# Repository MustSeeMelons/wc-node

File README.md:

# WC internet radio

Inspired by a restroom that welcomed me as I entered, played smooth jazz while I was inside, and even said goodbye as I left. A Raspberry Pi Zero W at the heart.

All audio playback is based on [this Adafruit article](https://learn.adafruit.com/adafruit-max98357-i2s-class-d-mono-amp/raspberry-pi-wiring).

Legacy 32-bit Pi OS is required for this to work.

## V1

Turns out using a sonar distance sensor for presence detection does not work very well. You might enter the room and stay out of range for a bit, thus triggering a leave. Then after a bit re-trigger it. Many edge cases, for proper operation switch should be on the door and the door must be auto-closing. Otherwise the user experience will be flawed.

Kept the sonar as the on/off switch. Made to just work without spending much time on the looks.

Consists of a Pi Zero W, MAX98357 and a HC-SR04. Everything is powored from the Pi. Suprisingly, sounds better than most laptops.

## V2

While the V1 worked well, it did not look the part. Also the sonar was a gimmick and it lacked physical volume controls that turned out more important than anticipated.

The sonar was replaced with a switch and a rotary encoder entered the fray. Turn it on/off with the switch and adjust the volume with the ring around the speaker.

Worked well enough, but it sounded worse. Propably because the speaker was not as enclosed as it was previsouly. The ring was also flimsy feeling. For some reason I used a rotary encoder from a mouse. Which is tiny and made positioning it harder. Also bearings would have been nice.

## V3

Time to make it louder and make it look even nicer. Made possible by a bunch of interconencted modules: 12V power to an Aliexpress amplifirer. Buck/boost module to step down 12V to 5V for the Pi. An PCM5102A module for turning the Pi's I2S signal into analogue audio. Non removable 12V power brick.

Operation requires pressing a button to turn on audio playback from the Pi and turning nob to turn off the amp and perform volume control.

Sounds better and overall is much more pleasing to the eye.

## V4

The final iteration: getting rid of the rats nest of modules and making an integrated PCB for all. About 1.5 years of learning electronics made it possible.

It works better as ever and propably is the final form.

Is it perfect? Hell no, but functional without major flaws as far as I know. The PCB layouts ignore `recomended layouts` from the datasheets so to be easier to hand solder.

The speaker size really should be placed into a wooded enclosure. Also the [stream](https://fmstream.org/) quality is a factor now.

# How to

- `sudo apt-get update`
- `npm i`
- `sudo apt-get install -y mpg123`
- `sudo npm start`
- `/etc/systemd/system/ateja.service`

# Node

- `use nvm to install node`
- `sudo ln -s $(which node) /usr/bin/node`
- `sudo ln -s $(which npm) /usr/local/bin/npm`

# A few commands to add to /boot/config.txt

`raspi-gpio set 20 pu`
`raspi-gpio set 4 pu`

# Systemd

- `sudo systemctl daemon-reload`
- `sudo systemctl start ateja`
- `journalctl -u ateja.service -f`
- `sudo systemctl status ateja`
- `sudo systemctl stop ateja`
- `sudo systemctl restart ateja`
- `sudo systemctl enable ateja`
- `sudo systemctl disable ateja`

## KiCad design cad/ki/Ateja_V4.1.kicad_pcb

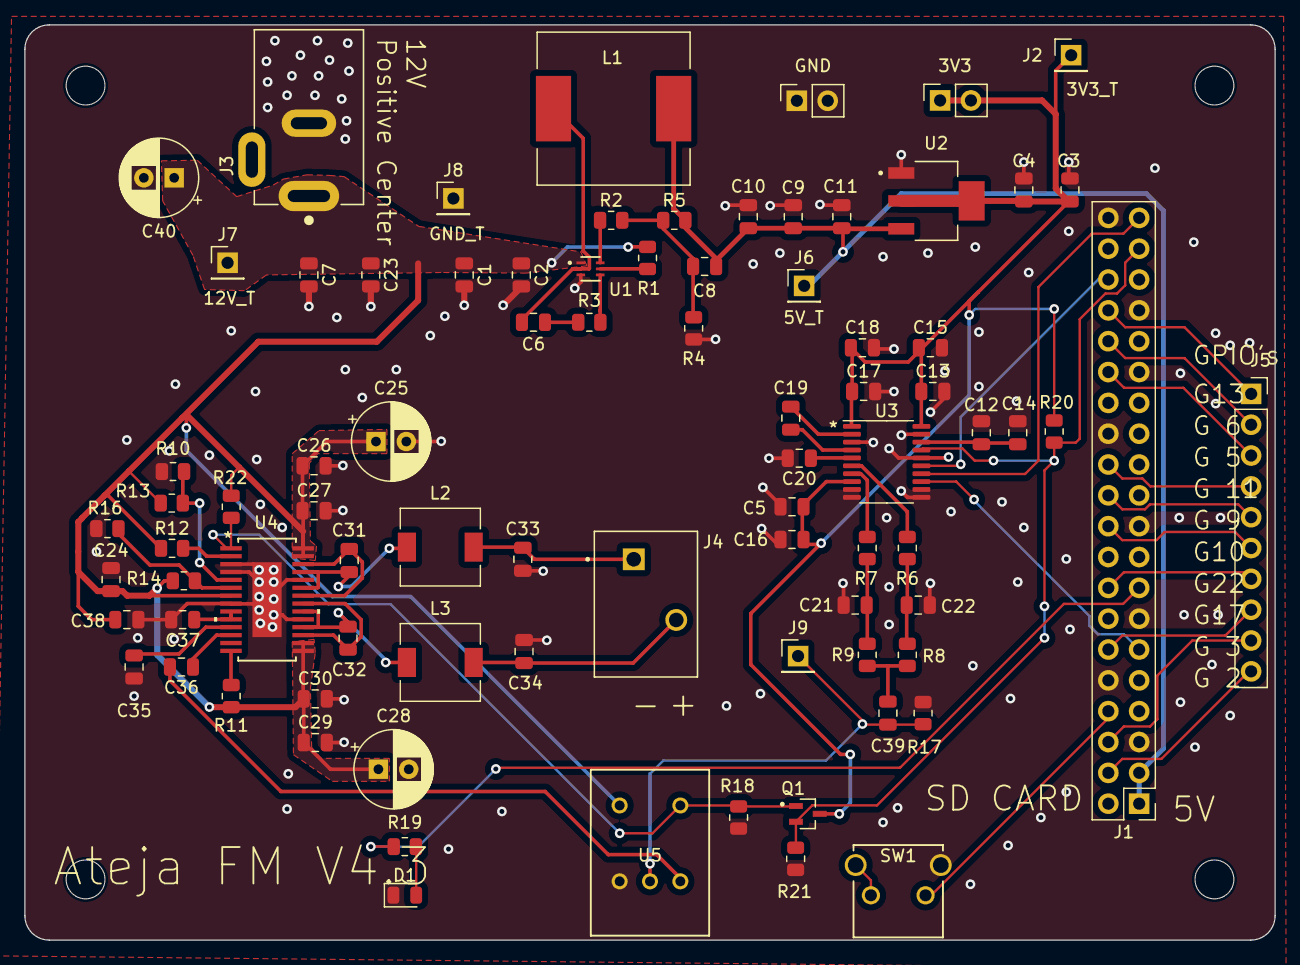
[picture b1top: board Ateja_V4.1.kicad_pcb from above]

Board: 2 copper layers, 103.0 x 75.4 mm, 87 parts (0 on the bottom side), 53 nets.

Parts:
C1, C9, C10, C23: 22uF; C_0805_2012Metric
C2, C7: 100 nF; C_0805_2012Metric
C3: 47 uF; C_0805_2012Metric
C4, C11: 1.5 uF; C_0805_2012Metric
C5, C12, C13, C17, C26, C29: 0.1uF; C_0805_2012Metric
C6, C24, C35, C36, C37, C38: 1 uF; C_0805_2012Metric
C8: 10 pF; C_0805_2012Metric
C14, C15, C16, C18, C39: 10 uF; C_0805_2012Metric
C19, C20: 2.2uF; C_0805_2012Metric
C21, C22: 2.2 nF; C_0805_2012Metric
C25, C28: 220 uF; CP_Radial_D6.3mm_P2.50mm
C27, C30: 1000pF; C_0805_2012Metric
C31, C32: 0.47uF; C_0805_2012Metric
C33, C34: 1uF; C_0805_2012Metric
C40: 100 uF; CP_Radial_D6.3mm_P2.50mm
D1: LED; LED_0805_2012Metric
H1, H2, H3, H4: MountingHole; MountingHole_3.2mm_M3
J1: Conn_02x20_Odd_Even; PinHeader_2x20_P2.54mm_Vertical
J2: 3V3_T; PinHeader_1x01_P2.54mm_Vertical
J3: PJ-202AH; CUI_PJ-202AH
J4: TBL002A-350-02GR-2OR; CUI_TBL002A-350-02GR-2OR
J5: Conn_01x10_Socket; PinSocket_1x10_P2.54mm_Vertical
J6: 5V5_T; PinHeader_1x01_P2.54mm_Vertical
J7: 12V_T; PinHeader_1x01_P2.54mm_Vertical
J8: GND_T; PinHeader_1x01_P2.54mm_Vertical
J9: I2S_T; PinHeader_1x01_P2.54mm_Vertical
J10, J11: Conn_01x02_Socket; PinSocket_1x02_P2.54mm_Vertical
L1: 4.7 uH; L_12x12mm_H6mm
L2, L3: 33uH; L_6.3x6.3_H3
Q1: 2N7002W; SOT65P220X100-3N
R1: 100k; R_0805_2012Metric
R2: 18k; R_0805_2012Metric
R3: 10 Ohm; R_0805_2012Metric
R4: 5.49k; R_0805_2012Metric
R5: 40.2k; R_0805_2012Metric
R6, R7, R8, R9, R17: 470 Ohm; R_0805_2012Metric
R10, R14, R20, R22: NC; R_0805_2012Metric
R11, R13, R16: 100K; R_0805_2012Metric
R12: 100k Ohm; R_0805_2012Metric
R18, R21: 1k Ohm; R_0805_2012Metric
R19: 1K; R_0805_2012Metric
SW1: 1825027-8; SW2_1825027-C_TEC
U1: MP1660GTF-Z; SOT563-6PIN_MNP
U2: TLV1117-33CDCYRG3; SOT230P700X180-4N
U3: PCM5102A; TSSOP-20_4.4x6.5mm_P0.65mm
U4: TPA3111D1PWPR; PWP28_6P17X2P4-M
U5: PTR901-2015K-B103; PTR901-2015K-B103_BRN

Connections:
/3V3: C3.1, C4.1, C5.1, C13.1, C15.1, C16.1, C17.1, C18.1, J2.1, J10.1, J10.2, Q1.3, R20.1, U2.2 (OUT), U2.4 (OUT), U3.1 (CPVDD), U3.8 (AVDD), U3.20 (DVDD)
/5V: C8.2, C9.1, C10.1, C11.1, J1.1, J1.3, J6.1, L1.2, R5.2, U2.3 (IN)
/AMP_SD: Q1.1, R18.2, R22.2, U4.1 (*SD), U5.6
/BCK: J1.11, U3.13 (BCK)
/DIN: J1.39, U3.14 (DIN)
/GPIO_2: J1.4, J5.10
/GPIO_3: J1.6, J5.9
/GPIO_5: J1.30, J5.3
/GPIO_6: J1.32, J5.2
/GPIO_9: J1.22, J5.5
/GPIO_10: J1.20, J5.6
/GPIO_11: J1.24, J5.4
/GPIO_13: J1.34, J5.1
/GPIO_17: J1.12, J5.8
/GPIO_22: J1.16, J5.7
/INP: C36.2, U5.3
/LED_ACTIVE: J1.15, R19.2
/LRCK: J1.36, U3.15 (LRCK)
/MUTE_LOW: J1.37, Q1.2, R20.2, R21.2, U3.17 (XSMT)
/POWER_OFF: J1.8, SW1.2
GND: C1.2, C2.2, C3.2, C4.2, C5.2, C7.2, C9.2, C10.2, C11.2, C12.2, C13.2, C14.2, C15.2, C16.2, C17.2, C18.2, C20.2, C21.2, C22.1, C23.2, C24.1, C25.2, C26.2, C27.2, C28.2, C29.2, C30.2, C33.1, C34.2, C35.2, C37.1, C38.2, C40.2, D1.1 (K), J1.5, J1.10, J1.13, J1.19, J1.26, J1.29, J1.33, J1.40, J3.2, J8.1, J11.1, J11.2, R4.1, R10.2, R16.2, R17.1, R18.1, R21.1, SW1.4, U1.3 (GND), U2.1 (ADJ/GND), U3.3 (CPGND), U3.9 (AGND), U3.10 (DEMP), U3.11 (FLT), U3.12 (SCK), U3.16 (FMT), U3.19 (DGND), U4.3 (GND), U4.4 (GND), U4.8 (AGND), U4.19 (PGND), U4.24 (PGND), U4.29 (EPAD), U5.1
unnamed: C6.2, R3.2
unnamed: C8.1, R2.2, R4.2, R5.1
unnamed: C21.1, R7.1, R9.2
unnamed: C22.2, R6.1, R8.2
unnamed: C31.1, U4.22 (BSN), U4.26 (BSN)
unnamed: C31.2, L2.1, U4.23 (OUTN), U4.25 (OUTN)
unnamed: C32.1, U4.17 (BSP), U4.21 (BSP)
unnamed: C32.2, L3.1, U4.18 (OUTP), U4.20 (OUTP)
unnamed: C33.2, J4.1, L2.2
unnamed: C34.1, J4.2, L3.2
unnamed: C39.1, R8.1, R9.1
unnamed: D1.2 (A), R19.1
unnamed: C39.2, J9.1, R17.2, U5.2
unnamed: R11.1, U4.14 (AVCC)
unnamed: SW1.1, SW1.3
unnamed: R3.1, U1.4 (BST)
unnamed: R1.2, U1.5 (EN)
unnamed: R2.1, U1.6 (FB)
unnamed: C6.1, L1.1, U1.2 (SW)
unnamed: C19.2, U3.4 (CAPM)
unnamed: C19.1, U3.2 (CAPP)
unnamed: C12.1, C14.1, U3.18 (LDOO)
unnamed: R6.2, U3.6 (OUTL)
unnamed: R7.2, U3.7 (OUTR)
unnamed: C20.1, U3.5 (VNEG)
unnamed: R12.2, U4.2 (*FAULT)
unnamed: R10.1, R13.1, U4.5 (GAIN0)
unnamed: R14.1, R16.1, U4.6 (GAIN1)
unnamed: C37.2, U4.9 (GVDD), U4.10 (PLIMIT)
unnamed: C35.1, U4.11 (INN)
unnamed: C36.1, U4.12 (INP)
VCC: C1.1, C2.1, C7.1, C23.1, C24.2, C25.1, C26.1, C27.1, C28.1, C29.1, C30.1, C38.1, C40.1, J3.1, J7.1, R1.1, R11.2, R12.1, R13.2, R14.2, R22.1, U1.1 (VIN), U4.7 (AVCC), U4.15 (PVCC), U4.16 (PVCC), U4.27 (PVCC), U4.28 (PVCC), U5.4

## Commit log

2021-03-30 Init
2021-03-30 Basic pin setup
2021-03-30 Sonar Test
2021-03-30 Partial Sonar
2021-03-31 Sad Sonar
2021-04-02 Different GPIO lib test
2021-04-02 Fixed state
2021-04-03 Fix LED pin
2021-04-03 Readme additions
2021-04-03 Audio test
2021-04-03 Trying to play sounds!
2021-04-03 Commenty
2021-04-03 yeet
2021-04-03 Audio play works!
2021-04-03 Voice things
2021-04-03 Music fade in & fade out
2021-04-04 Fade in/fade out playing sound
2021-04-04 Fix a few refactor issues
2021-04-04 Stream test
2021-04-04 Stream fix
2021-04-04 Config file
2021-04-04 Stream url change web interface
2021-04-04 Play stream web toggle
2021-04-04 Stop all audio
2021-04-04 File upload
2021-04-04 Audio file selection
2021-04-04 Fix path, add more info
2021-04-05 Refactor flow, web sound options WIP
2021-04-05 Min/Max/VolStep web configuration
2021-04-05 Message animation
2021-04-05 Web on/off toggle
2021-04-05 Minor tweaks
2021-04-05 PWA test
2021-04-05 Fix startup state
2021-04-07 Better notifications, systemd setuo
2021-04-07 Fix config manager
2021-04-07 Restore proper index
2021-04-07 Fix readme
2021-04-07 Phixed audio manager paths
2021-04-07 Bug Hunt
2021-04-07 Added moar features to the redme
2021-04-08 Date to string fix
2021-04-08 Service restart test
2021-04-08 Simplify restart
2021-04-14 Sonar toggle
2021-04-14 Update readme, remove delay
2021-04-14 Express fix
2021-04-14 Restore some rest time
2021-04-14 Move wait around
2021-04-14 Restore original wait
2021-04-14 Restore to old
2021-04-14 Add in the pesky await
2021-04-14 Remove if
2021-04-14 More wait if sonar disabled
2021-04-14 Shutdown option, splash screen
2021-04-14 Fixed urls
2021-04-15 Socket test
2021-04-18 Stashing
2021-04-18 Title processing
2021-04-18 Stream output data parse
2021-04-18 Now playing HTML
2021-04-20 Stream Management Test
2021-04-20 Restore index
2021-04-20 Fix stream playback
2021-04-20 Handling deleted streams better
2021-04-20 Cleanup
2021-04-20 Remove scandir
2021-05-22 Tweak sonar & LED behavior
2021-05-22 Phix oopsie
2021-07-07 Add wait before fade in audio
    To avoid when it starts at full blast
2021-07-20 Turn on led before fadeout, a bit moar wait.
    Started to turn off on itself..
2021-07-20 Change next sonar state on api call too
2022-07-28 V2 init
2022-07-28 Got rotary to work
2022-08-03 Removed interrupts
2022-08-22 Interference woes
2022-08-26 Alert pwr button test
2022-08-26 onoff test
2022-08-26 Lib fix
2022-08-26 Add rotary interrupt, pwr log
2022-08-26 Uncomment stuff..
2022-08-26 Rotary works, pwr not
2022-08-26 Pwr works as well
2022-08-27 Add debounces
2022-08-27 Tweak boundies
2022-08-27 Audio volume by rotaty
2022-08-27 Log col changes
2022-08-27 New rotary vol logic
2022-08-27 Vol twiks
2022-08-27 Twiks
2022-08-28 Add logs back
2022-08-28 Fix audio change
2022-09-15 Increase rotary debounce
2022-09-15 Rotary read cahnge
2022-09-15 Fix oopsie
2022-09-15 Revert
2022-09-15 Large debounce
2022-09-15 Table try
2022-09-15 Use new logic
2022-09-15 Phix wrong chevron
2022-09-15 Add logs
2022-09-15 Phix
2022-09-15 restore old
2022-09-15 It was a loose wire, removed sonar
2022-09-17 LED pwm
2022-09-23 Remove sonar stuff from script
2022-11-07 Some old changes
2022-11-07 Type phic
2022-11-07 Add max volume show
2022-11-07 Smol fixie
2024-02-26 Add pic
2024-02-26 Update rid me
2024-08-30 Update TODOs
2024-08-30 New features, cleanup the old
2024-08-31 Finishing touches
2024-09-01 Update readme, cleanup old code
    It is done.
2024-09-01 Fix some borks
